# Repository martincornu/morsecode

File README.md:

# morsecode
Interpretation of morse code from light for an escape room.

The player must make a Morse code defined by making headlights calls with a car.

Electronic:

PCB design:

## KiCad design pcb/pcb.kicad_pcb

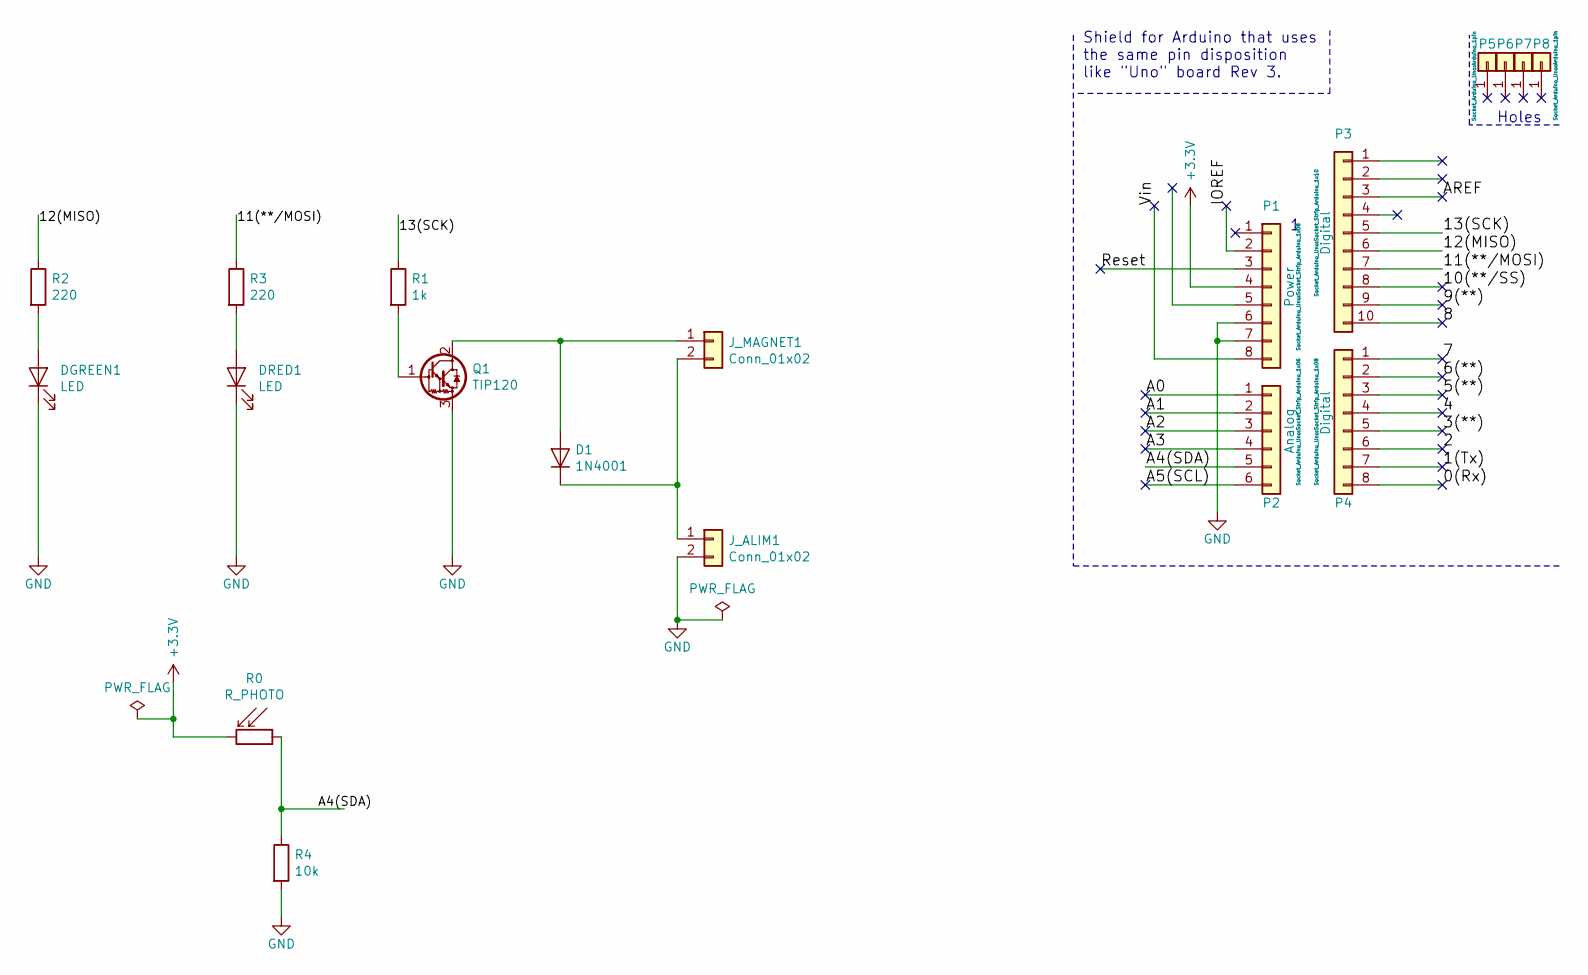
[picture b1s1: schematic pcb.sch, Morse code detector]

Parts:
D1: 1N4001; D_DO-41_SOD81_P10.16mm_Horizontal
DGREEN1: LED; PinHeader_1x02_P2.54mm_Vertical
DRED1: LED; PinHeader_1x02_P2.54mm_Vertical
J_ALIM1: Conn_01x02; TerminalBlock_bornier-2_P5.08mm
J_MAGNET1: Conn_01x02; TerminalBlock_bornier-2_P5.08mm
P1: Power; Socket_Strip_Arduino_1x08
P2: Analog; Socket_Strip_Arduino_1x06
P3: Digital; Socket_Strip_Arduino_1x10
P4: Digital; Socket_Strip_Arduino_1x08
P5, P6, P7, P8: CONN_01X01; Arduino_1pin
Q1: TIP120; TO-220-3_Vertical
R0: R_PHOTO; PinHeader_1x02_P2.54mm_Vertical
R1: 1k; R_Axial_DIN0309_L9.0mm_D3.2mm_P12.70mm_Horizontal
R2, R3: 220; R_Axial_DIN0309_L9.0mm_D3.2mm_P12.70mm_Horizontal
R4: 10k; R_Axial_DIN0309_L9.0mm_D3.2mm_P12.70mm_Horizontal

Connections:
+3V3: P1.4, R0.2
/0(Rx): P4.8
/1(Tx): P4.7
/2: P4.6
/3(**): P4.5
/4: P4.4
/5(**): P4.3
/6(**): P4.2
/7: P4.1
/8: P3.10
/9(**): P3.9
/10(**/SS): P3.8
/11(**/MOSI): P3.7, R3.1
/12(MISO): P3.6, R2.1
/13(SCK): P3.5, R1.1
/A0: P2.1
/A1: P2.2
/A2: P2.3
/A3: P2.4
/A4(SDA): P2.5, R0.1, R4.1
/A5(SCL): P2.6
/AREF: P3.3
/IOREF: P1.2
/Reset: P1.3
/Vin: P1.8
GND: DGREEN1.1 (K), DRED1.1 (K), J_ALIM1.2, P1.6, P1.7, Q1.3 (E), R4.2
unnamed: D1.1 (K), J_ALIM1.1, J_MAGNET1.2
unnamed: D1.2 (A), J_MAGNET1.1, Q1.2 (C)
unnamed: DGREEN1.2 (A), R2.2
unnamed: DRED1.2 (A), R3.2
unnamed: Q1.1 (B), R1.2

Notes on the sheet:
Holes
Shield for Arduino that uses the same pin disposition like "Uno" board Rev 3.

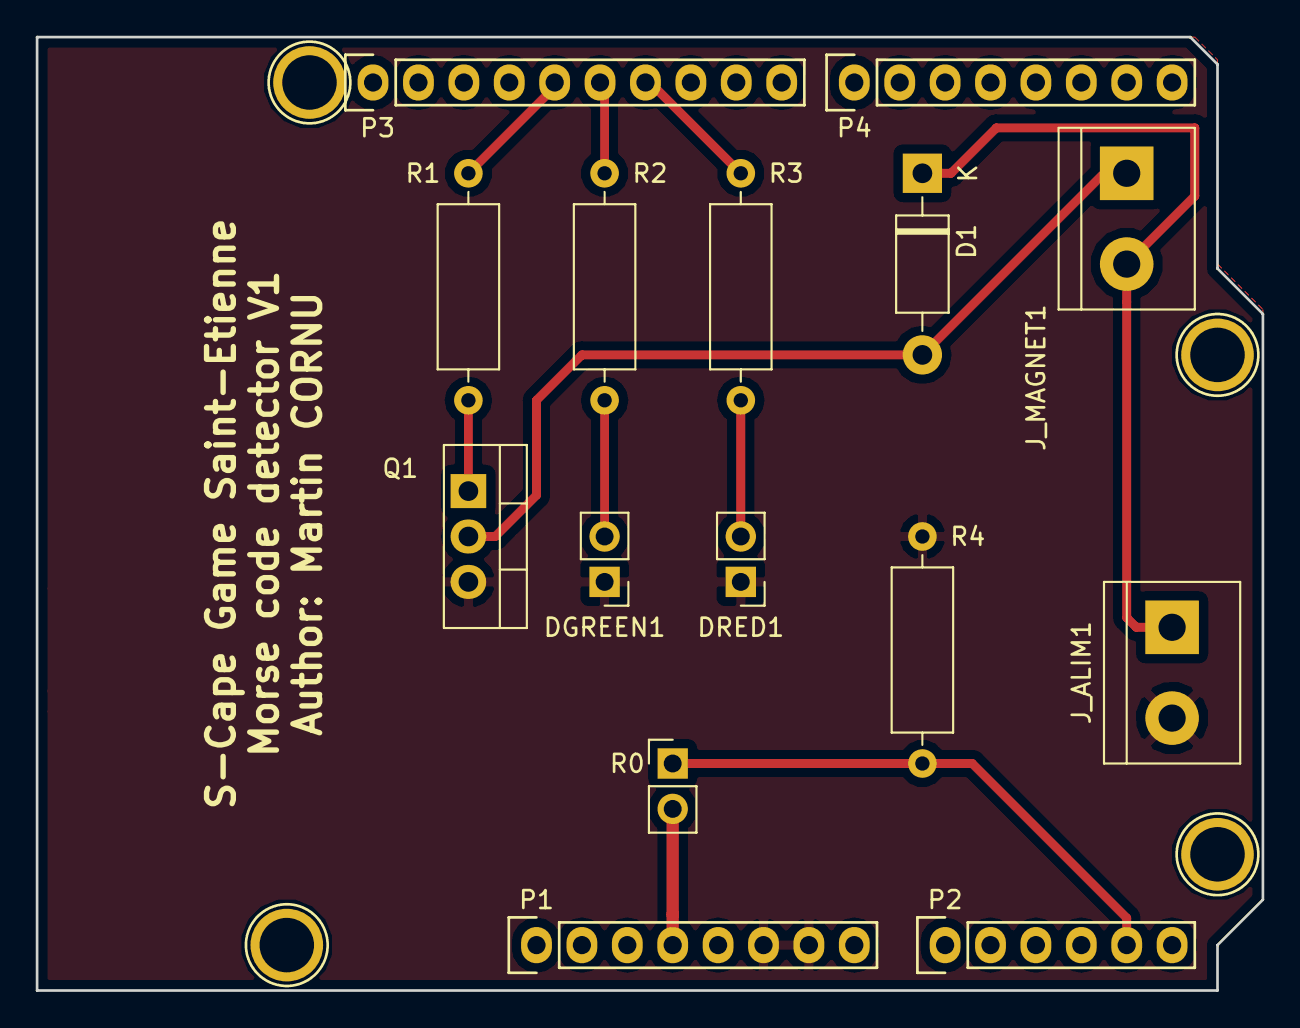
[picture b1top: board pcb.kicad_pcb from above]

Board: 2 copper layers, 68.6 x 53.3 mm, 19 parts (0 on the bottom side), 11 nets.

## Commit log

2018-11-02 detect suite, blink green if ok, red if not. Don't manage if message shorter yet.
2018-11-03 final version
2018-12-26 change dot's length and add electric scheme
2018-12-31 finished Kicad sch, pcb and gerbers files
2019-02-09 fix sch and pcb bug: diode connect to magnet now
